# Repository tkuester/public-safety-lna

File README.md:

# Public Safety LNA / Bandpass Filter

## Electrical Specification

 * Filter Passband: 729 to 960 MHz
 * Filter Insertion Loss: ~2 dB
 * Input Max: +15 dBm
 * LNA Gain: Approx +15 dB
 * Combined Gain: Approx 13 dB

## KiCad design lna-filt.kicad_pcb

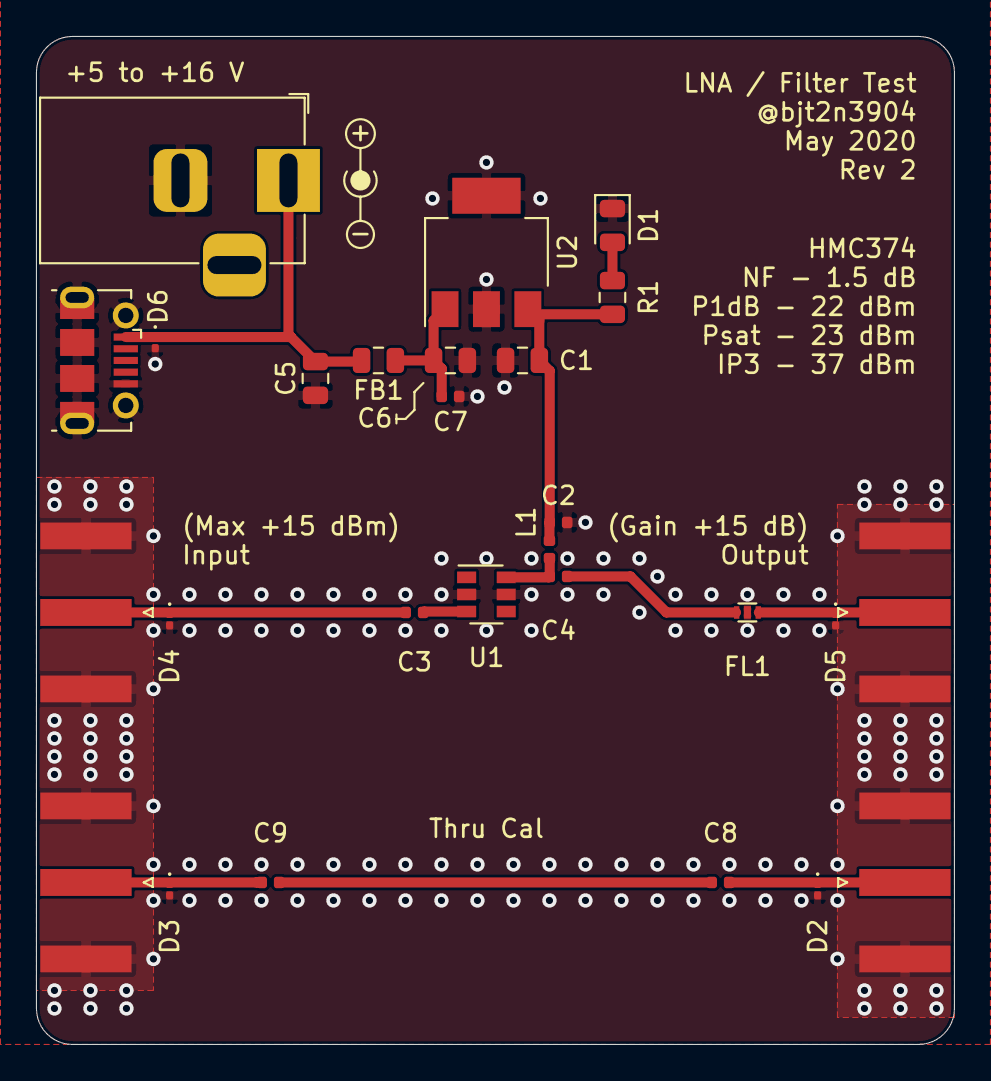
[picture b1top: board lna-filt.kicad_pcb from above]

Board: 2 copper layers, 51.0 x 56.0 mm, 27 parts (0 on the bottom side), 13 nets.

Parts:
C1, C5, C6: 4.7u; C_0805_2012Metric
C2: 1n; C_0402_1005Metric
C3, C4, C8, C9: 150p; C_0402_1005Metric
C7: 100n; C_0402_1005Metric
D1: LED; LED_0805_2012Metric
D2, D3, D4, D5, D6: ESD101; D_0201_0603Metric
FB1: Ferrite_Bead_Small; R_0805_2012Metric
FL1: FI168B0845D9-T
J1, J2, J5, J6: Conn_Coaxial; SMA_Amphenol_132289_EdgeMount
J3: Barrel_Jack; BarrelJack_Horizontal
J4: USB_B_Micro; USB_Micro-B_Molex-105017-0001
L1: 27n; L_0402_1005Metric
R1: R; R_0805_2012Metric
U1: HMC374; SOT-23-6
U2: MCP1703A-3302_SOT223; SOT-223-3_TabPin2

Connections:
+3V3: C1.2, C2.2, L1.1, R1.2, U2.3
+5V: C5.2, D6.1, FB1.2, J3.1, J4.1
GND: C1.1, C2.1, C5.1, C6.1, C7.1, D1.1, D2.2, D3.2, D4.2, D5.2, D6.2, FL1.2, J1.2, J2.2, J3.2, J4.5, J4.6, J5.2, J6.2, U1.2, U1.5, U2.2
unnamed: C3.1, U1.3
unnamed: C3.2, D4.1, J1.1
unnamed: C4.1, FL1.1
unnamed: C4.2, L1.2, U1.6
unnamed: C6.2, C7.2, FB1.1, U2.1
unnamed: C8.1, C9.2
unnamed: C8.2, D2.1, J5.1
unnamed: C9.1, D3.1, J6.1
unnamed: D1.2, R1.1
unnamed: D5.1, FL1.3, J2.1

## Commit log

2020-05-25 Adding first generation of release files
2020-05-25 Move LED to 3V3, add power silk screen
    Closes #2
2020-05-25 Removing thermals for SMA, fixing SMA short
    The SMA connectors were not close enough to the edge of the PCB. A thin
    strip of copper went under the center pin, and would short it to ground.
    By bumping the connector closer to the PCB edge, we remove the short.
    Closes #1.
